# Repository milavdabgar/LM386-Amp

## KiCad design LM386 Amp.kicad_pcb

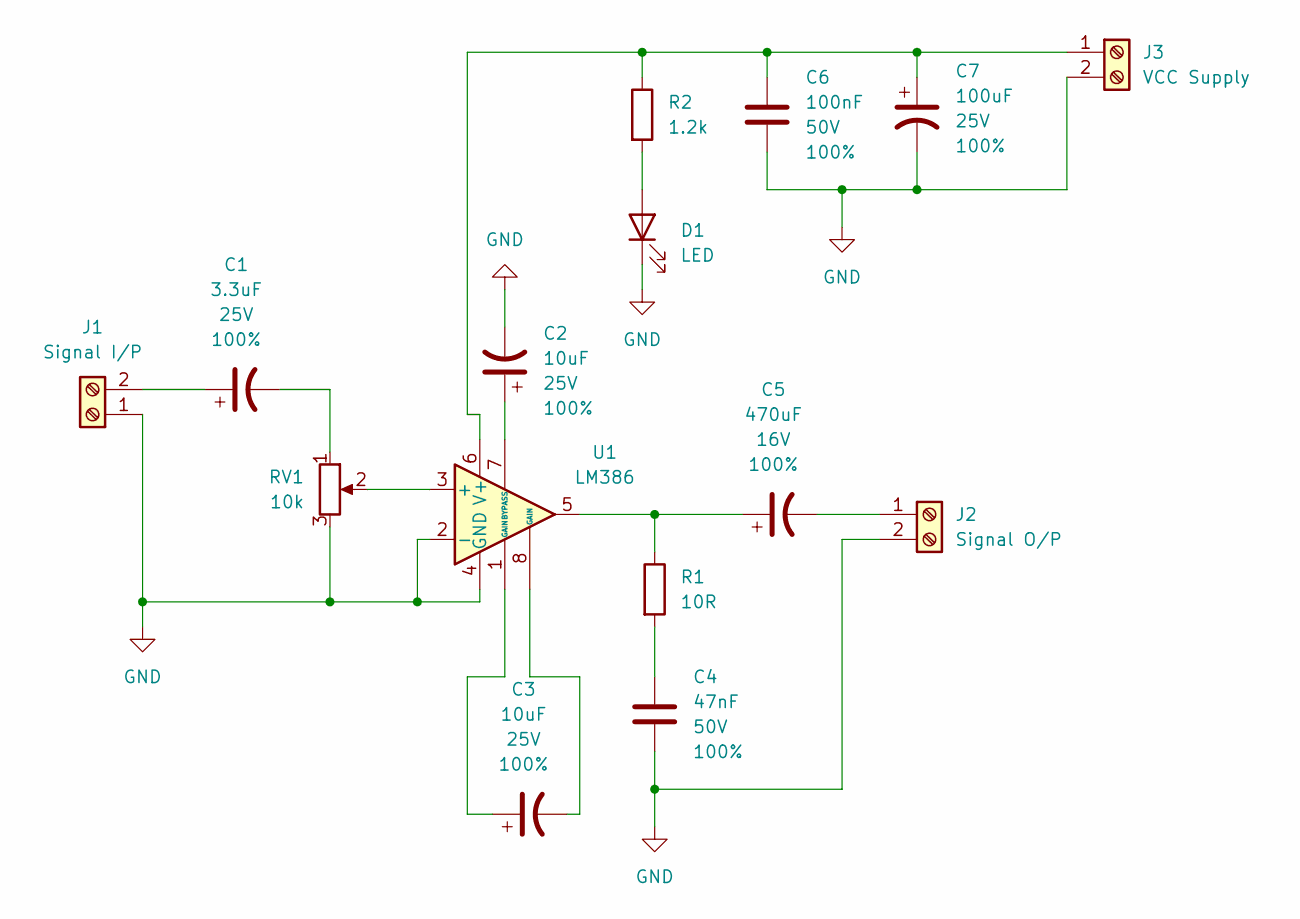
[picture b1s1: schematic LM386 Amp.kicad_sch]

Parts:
C1: 3.3uF; CP_Radial_D5.0mm_P2.50mm; Voltage 25V; Tolerance 100%
C2, C3: 10uF; CP_Radial_D5.0mm_P2.50mm; Voltage 25V; Tolerance 100%
C4: 47nF; C_Disc_D5.0mm_W2.5mm_P5.00mm; Voltage 50V; Tolerance 100%
C5: 470uF; CP_Radial_D8.0mm_P3.50mm; Voltage 16V; Tolerance 100%
C6: 100nF; C_Disc_D5.0mm_W2.5mm_P5.00mm; Voltage 50V; Tolerance 100%
C7: 100uF; CP_Radial_D6.3mm_P2.50mm; Voltage 25V; Tolerance 100%
D1: LED; LED_D3.0mm
J1: Signal I/P; TerminalBlock_Phoenix_PT-1,5-2-3.5-H_1x02_P3.50mm_Horizontal
J2: Signal O/P; TerminalBlock_Phoenix_PT-1,5-2-3.5-H_1x02_P3.50mm_Horizontal
J3: VCC Supply; TerminalBlock_Phoenix_PT-1,5-2-3.5-H_1x02_P3.50mm_Horizontal
R1: 10R; R_Axial_DIN0207_L6.3mm_D2.5mm_P7.62mm_Horizontal
R2: 1.2k; R_Axial_DIN0207_L6.3mm_D2.5mm_P7.62mm_Horizontal
RV1: 10k; Potentiometer_Piher_T-16H_Single_Horizontal
U1: LM386; DIP-8_W7.62mm_Socket

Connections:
GND: C2.2, C4.2, C6.2, C7.2, D1.1 (K), J1.1, J2.2, J3.2, RV1.3, U1.2 (-), U1.4 (GND)
unnamed: C1.2, RV1.1
unnamed: C3.1, U1.1 (GAIN)
unnamed: C3.2, U1.8 (GAIN)
unnamed: C4.1, R1.2
unnamed: C5.1, R1.1, U1.5
unnamed: D1.2 (A), R2.2
unnamed: C1.1, J1.2
unnamed: C5.2, J2.1
unnamed: C6.1, C7.1, J3.1, R2.1, U1.6 (V+)
unnamed: RV1.2, U1.3 (+)
unnamed: C2.1, U1.7 (BYPASS)

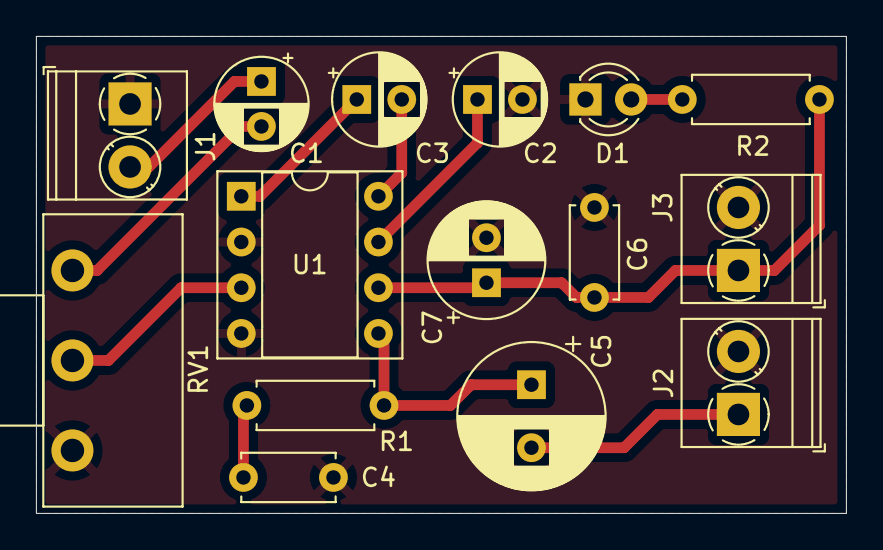
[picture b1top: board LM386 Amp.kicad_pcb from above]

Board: 2 copper layers, 45.0 x 26.5 mm, 15 parts (0 on the bottom side), 12 nets.

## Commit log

2024-08-30 Init
